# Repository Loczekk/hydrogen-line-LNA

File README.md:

PL below
<!-- TABLE OF CONTENTS -->

<details> <summary>Table of Contents</summary> 
  <ol> 
    <li><a href="#introduction">Introduction</a></li> 
    <li><a href="#final-parameters">Final Parameters</a></li> 
    <li><a href="#measurements">Measurements</a></li> 
  </ol> 
</details>

<!-- INTRODUCTION -->
## Introduction
The aim of the project was to design, build and test a low noise amplifier operating in the L-band. The amplifier was to meet strict requirements for gain (> 30 dB) and noise figure less than 1 dB.
A two-stage amplifier was implemented as a PCB on RF4 laminate and then subjected to detailed measurements to verify its performance. Scattering parameters, noise figure, 1 dB compression point, harmonic and third-order intermodulation distortion were measured.
Based on the results, it was concluded that the amplifier meets most of the design requirements: gain of 35.15 dB, output matching of 12.68 dB and 1-dB compression point at 3.02 dBm. Only the noise figure exceeded the assumed value and reached 1.39 dB, which, however, does not disqualify it from applications in radio astronomy.
Additionally, an automatic biasing circuit for the LNA was designed to ensure the correct power-up voltage sequence.
<p align="right">(<a href="#readme-top">back to top</a>)</p>

## Final Parameters
<h3>Key Parameters (for <strong>f = 1420 MHz</strong>)</h3>

<table>
  <thead>
    <tr>
      <th>Parameter</th>
      <th>Value</th>
      <th>Requirement</th>
    </tr>
  </thead>
  <tbody>
    <tr>
      <td>Gain</td>
      <td>35.15 dB</td>
      <td>&gt; 30 dB</td>
    </tr>
    <tr>
      <td>Noise figure</td>
      <td>1.39 dB</td>
      <td>&lt; 1 dB</td>
    </tr>
    <tr>
      <td>Output matching (<i>S<sub>22</sub></i>)</td>
      <td>12.68 dB</td>
      <td>&gt; 10 dB</td>
    </tr>
    <tr>
      <td>Compression point (<i>P<sub>1dB</sub></i>)</td>
      <td>3.02 dBm</td>
      <td>&gt; 0 dBm</td>
    </tr>
    <tr>
      <td>THD (for <i>P<sub>IN</sub></i> = –40 dBm)</td>
      <td>–47.21 dB</td>
      <td>–</td>
    </tr>
    <tr>
      <td>IP3 (for <i>P<sub>IN</sub></i> = –40 dBm)</td>
      <td>19.09 dBm</td>
      <td>–</td>
    </tr>
  </tbody>
</table>
<p align="right">(<a href="#readme-top">back to top</a>)</p>

## Measurements
<h3>S11 and S22 parameters to compare with simulate</h3>

<h3>Gain and Noise to compare with simualation</h3>

<h3>All S parameters</h3>

<p align="right">(<a href="#readme-top">back to top</a>)</p>

Wyniki mojej pracy inżynierskiej, całość udostępniona w formie PDF.

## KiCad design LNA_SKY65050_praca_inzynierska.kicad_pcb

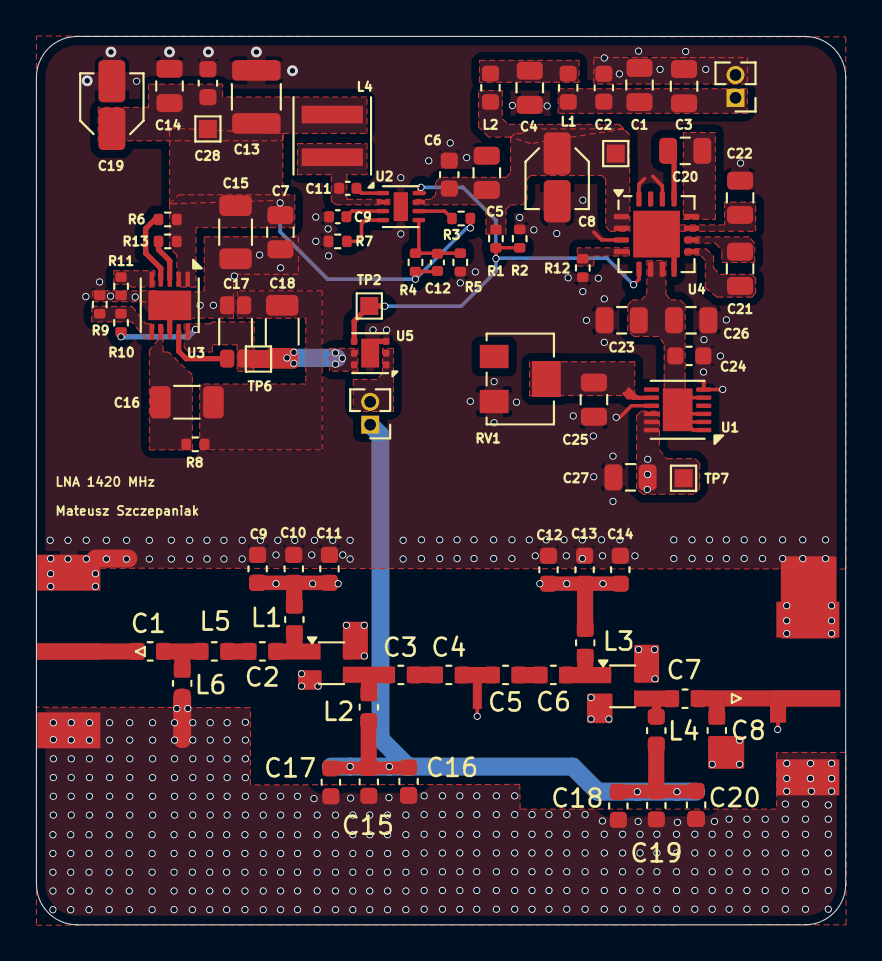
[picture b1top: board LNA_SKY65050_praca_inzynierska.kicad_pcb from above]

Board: 4 copper layers, 45.0 x 49.4 mm, 82 parts (0 on the bottom side), 29 nets.

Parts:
C1, C2, C3#2, C4, C5#2, C6#2, C7, C8#2, C9#2, C10, C11, C12, C13#2, C14#2, C15#2, C16, C17#2, C18, C19, C20#2: C_0603_1608Metric
C1#2, C20, C21: 1u; C_0805_2012Metric
C2#2: 0.1u; C_0603_1608Metric
C3, C4#2, C5, C7#2, C14, C25, C26: 4,7u; C_0805_2012Metric
C6: 0,1u; C_0603_1608Metric
C8, C19#2: 22u; C_Elec_3x5.4
C9: 1u; C_0402_1005Metric
C11#2: 0,1u; C_0402_1005Metric
C12#2: 10p; C_0402_1005Metric
C13: 47u; C_1210_3225Metric
C15: C; C_1206_3216Metric
C16#2, C17: 4,7u; C_1206_3216Metric
C18#2: opt; C_1206_3216Metric
C22, C27: 10u; C_0805_2012Metric
C23: 2,2u; C_0805_2012Metric
C24: 0,01u; C_0603_1608Metric
C28: 22u; C_0603_1608Metric
J1: Conn_01x02_Pin; PinHeader_1x02_P1.27mm_Vertical
J2: Id; PinHeader_1x02_P1.27mm_Vertical
L1: FB; L_0603_1608Metric
L1#2, L2#2, L3, L4, L5, L6: C_0603_1608Metric
L2: 0; L_0603_1608Metric
L4#2: 2,2u; L_Coilcraft_XxL4020
R1, R4: 1M; R_0402_1005Metric
R2: opt; R_0402_1005Metric
R3: 100k; R_0402_1005Metric
R5: 187k; R_0402_1005Metric
R6: 200k; R_0402_1005Metric
R7: 18,2k; R_0402_1005Metric
R8, R9: 30k; R_0402_1005Metric
R10: 453k; R_0402_1005Metric
R11: 510; R_0402_1005Metric
R12: 110k; R_0402_1005Metric
R13: 0; R_0402_1005Metric
RV1: 100k; Potentiometer_Bourns_3224W_Vertical
TP1: Vin; TestPoint_Pad_1.0x1.0mm
TP2: EN; TestPoint_Pad_1.0x1.0mm
TP3: 5V; TestPoint_Pad_1.0x1.0mm
TP6: 3V; TestPoint_Pad_1.0x1.0mm
TP7: Vgg; TestPoint_Pad_1.0x1.0mm
U1: LT3094xDD; DFN-12-1EP_3x3mm_P0.45mm_EP1.65x2.38mm
U2: LT8608; DFN-8-1EP_2x2mm_P0.5mm_EP0.8x1.6mm
U3: LT3042; DFN-10-1EP_3x3mm_P0.5mm_EP1.65x2.38mm
U4: ADP5600; LFCSP-16-1EP_4x4mm_P0.65mm_EP2.6x2.6mm
U5: ADP197-02; LFCSP-6-1EP_2x2mm_P0.65mm_EP1x1.6mm

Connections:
GND: C1#2.2, C2#2.2, C3.2, C4#2.2, C5.2, C6.2, C7#2.2, C8.2, C9.2, C9#2.1, C10.1, C11.1, C12.1, C13.1, C13#2.1, C14.1, C14#2.1, C15.2, C15#2.2, C16.2, C16#2.2, C17.2, C17#2.2, C18.2, C18#2.2, C19.2, C19#2.2, C20#2.2, C22.2, C23.2, C24.2, C25.2, C26.1, C27.2, C28.2, J1.2, L6.1, R2.2, R5.1, R7.1, R8.2, R9.2, R11.2, R12.2, RV1.3, U1.6 (ILIM), U1.9 (GND), U2.9 (GND), U3.8 (GND), U3.11 (GND), U4.3 (SYNC), U4.14 (SEL2), U4.16 (GND), U5.3 (GND), U5.7 (EP)
unnamed: C4#2.1, L1.2, L2.1
unnamed: C7#2.1, C12#2.2, C13.2, C14.2, C15.1, C19#2.1, C28.1, L4#2.2, R3.2, R4.2, R6.1, R13.1, TP3.1, U3.1 (IN), U3.2 (IN)
unnamed: C1#2.1, C2#2.1, C3.1, J1.1, L1.1
unnamed: J2.2, U5.1 (VOUT), U5.2 (VOUT)
unnamed: C23.1, C24.1, C26.2, U1.1 (IN), U1.2 (IN), U1.3 (EN/UV), U1.5 (PGFB), U1.13 (IN), U4.6 (FB), U4.7 (LDO_OUT)
unnamed: C25.1, RV1.2, U1.8 (SET)
unnamed: C11#2.1, U2.1 (BST)
unnamed: R1.2, R2.1, TP2.1, U2.8 (EN/UV), U4.5 (PGOOD), U5.4 (EN)
unnamed: C12#2.1, R4.1, R5.2, U2.5 (FB)
unnamed: R3.1, U2.6 (PG)
unnamed: R7.2, U2.4 (RT)
unnamed: C11#2.2, L4#2.1, U2.2 (SW)
unnamed: C9.1, U2.3 (Vcc)
unnamed: C5.1, C6.1, C8.1, L2.2, R1.1, TP1.1, U2.7 (Vin), U4.1 (Vin), U4.2 (EN)
unnamed: R13.2, U3.3 (EN/UV)
unnamed: R11.1, U3.5 (ILIM_)
unnamed: R6.2, U3.4 (PG)
unnamed: R9.1, R10.2, U3.6 (PGFB)
unnamed: C16#2.1, R8.1, U3.7 (SET)
unnamed: C20.1, U4.12 (C1+)
unnamed: C20.2, U4.13 (C1-)
unnamed: C21.1, U4.10 (C2+)
unnamed: C21.2, U4.9 (C2-)
unnamed: C22.1, U4.8 (CPOUT), U4.11 (CPOUT), U4.17 (EP)
unnamed: R12.1, U4.4 (FREQ)
Vd_3V: C17.1, C18#2.1, R10.1, TP6.1, U3.9 (OUTS), U3.10 (OUT), U5.5 (VIN), U5.6 (VIN)
Vd_prottected: C15#2.1, C16.1, C17#2.1, C18.1, C19.1, C20#2.1, J2.1, L2#2.1, L4.1
Vgg: C9#2.2, C10.2, C11.2, C12.2, C13#2.2, C14#2.2, C27.1, L1#2.2, L3.2, TP7.1, U1.10 (OUTS), U1.11 (OUT), U1.12 (OUT)

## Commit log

2025-08-06 Rename S we do porownania.png to images/S we do porownania.png
2025-08-06 Rename gotowy.jpg to images/gotowy.jpg
2025-08-06 Rename parametryS.png to images/parametryS.png
2025-08-06 Rename parametry_porownanie.png to images/parametry_porownanie.png
